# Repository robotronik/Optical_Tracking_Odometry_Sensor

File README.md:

Robotronik Optical Tracking Odometry Sensor
========================================

![Robotronik Optical Tracking Odometry Sensor [SEN-24904]](assets/img/otos_1.png)

[*Robotronik Optical Tracking Odometry Sensor [SEN-24904]*](https://www.sparkfun.com/products/24904)

The Robotronik Optical Tracking Odometry Sensor empowers you to elevate your robot's navigation capabilities with exceptional precision and streamlined integration. This compact, all-in-one sensor leverages the power of the PAA5163E1 chip from PixArt Imaging Inc., delivering accurate dual-axis motion data across various hard floor surfaces. But that's not all! This sensor boasts a powerful built-in 6-axis Inertial Measurement Unit (IMU) and an onboard microcontroller that performs real-time sensor fusion and tracking algorithms.

Repository Contents
-------------------

* **/Hardware** - Kicad 9 Design
* **/Production** - Production panel files

Documentation
--------------
* **[Arduino Library](https://github.com/sparkfun/SparkFun_Qwiic_OTOS_Arduino_Library)** - Arduino library for the SparkFun Optical Tracking Odometry Sensor.
* **[Hookup Guide](https://docs.sparkfun.com/SparkFun_Optical_Tracking_Odometry_Sensor/)** - Hookup guide for the SparkFun Optical Tracking Odometry Sensor.

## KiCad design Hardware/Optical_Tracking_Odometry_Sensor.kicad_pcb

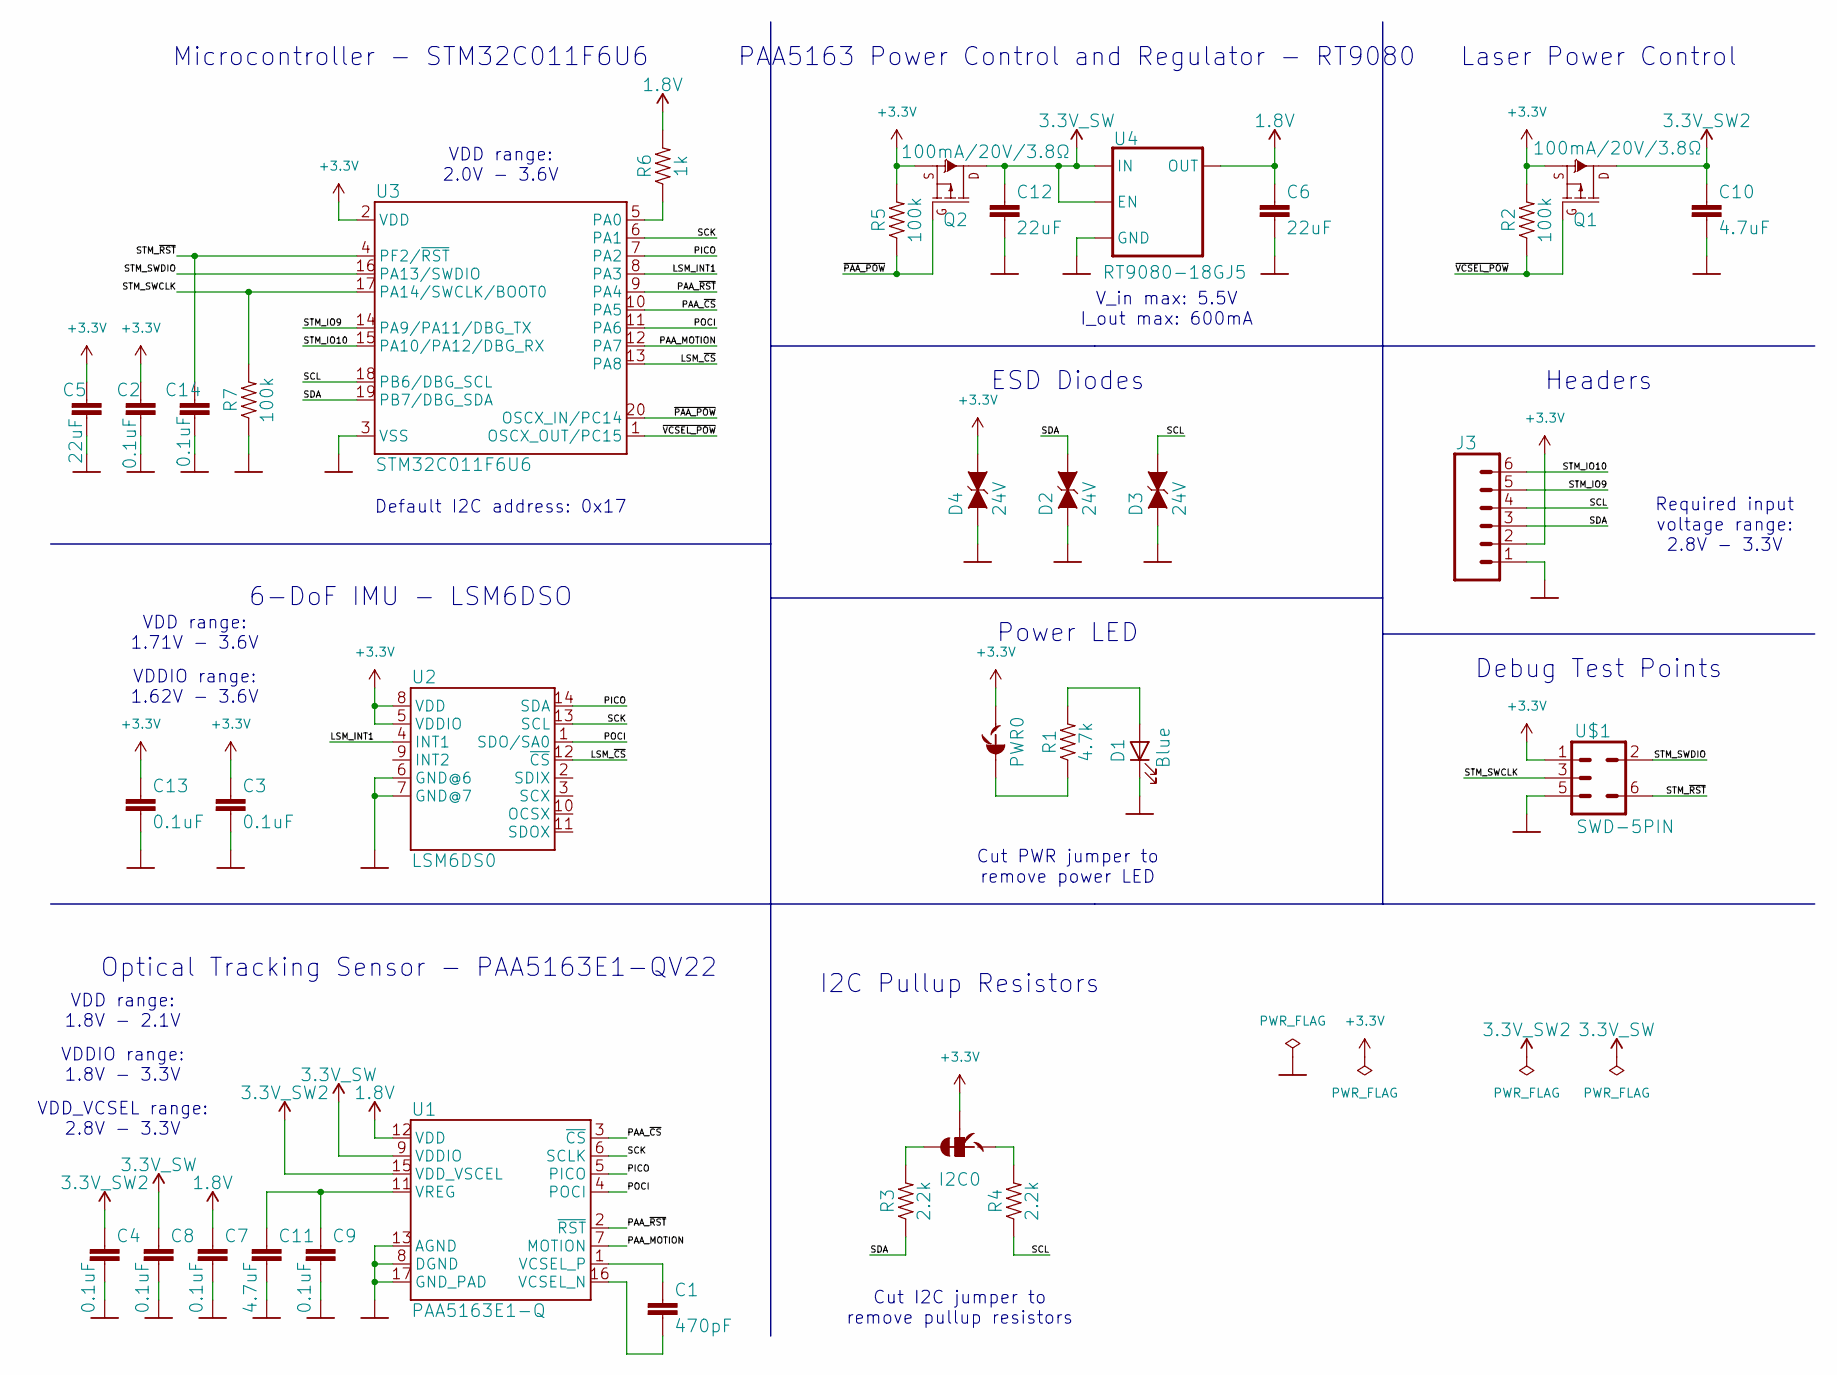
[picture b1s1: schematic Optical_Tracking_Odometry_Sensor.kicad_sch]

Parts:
C1: 470pF; C_0603_1608Metric
C2, C3, C4, C7, C8, C9, C13, C14: 0.1uF; C_0603_1608Metric
C5, C6, C12: 22uF; C_0603_1608Metric
C10, C11: 4.7uF; C_0603_1608Metric
D1: Blue; LED_0603_1608Metric
D2, D3, D4: 24V; D_0603_1608Metric
I2C0: JUMPER-SMT_3_2-NC_TRACE_SILK; SMT-JUMPER_3_2-NC_TRACE_SILK
J3: CONN_06NO_SILK_NO_POP; 1X06_NO_SILK
PWR0: JUMPER-SMT_2_NC_TRACE_SILK; SMT-JUMPER_2_NC_TRACE_SILK
Q1, Q2: 100mA/20V/3.8Ω; SOT-416
R1: 4.7k; R_0603_1608Metric
R2, R5, R7: 100k; R_0603_1608Metric
R3, R4: 2.2k; R_0603_1608Metric
R6: 1k; R_0603_1608Metric
U1: PAA5163E1-Q
U2: LSM6DS0; LGA-14_3x2.5mm_P0.5mm_LayoutBorder3x4y
U3: STM32C011F6U6; ST_UFQFPN-20_3x3mm_P0.5mm
U4: RT9080-18GJ5; SOT-23-5
U$1: SWD-5PIN; PAD_05_03X2_TP_NO4

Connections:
1.8V: C6.1, C7.1, R6.2, U1.12 (VDD), U4.5 (OUT)
3.3V_SW: C8.1, C12.1, Q2.3 (D), U1.9 (VDDIO), U4.1 (IN), U4.3 (EN)
3.3V_SW2: C4.1, C10.1, Q1.3 (D), U1.15 (VDD_VSCEL)
+3.3V: C2.1, C3.1, C5.1, C13.1, D4.2 (C), I2C0.2, J3.2, PWR0.2, Q1.2 (S), Q2.2 (S), R2.2, R5.2, U2.5 (VDDIO), U2.8 (VDD), U3.2 (VDD), U$1.1
/LSM_INT1: U2.4 (INT1), U3.8 (PA3)
/LSM_~CS: U2.12 (~CS), U3.13 (PA8)
/PAA_MOTION: U1.7 (MOTION), U3.12 (PA7)
/PAA_~CS: U1.3 (~CS), U3.10 (PA5)
/PAA_~RST: U1.2 (~RST), U3.9 (PA4)
/PICO: U1.5 (PICO), U2.14 (SDA), U3.7 (PA2)
/POCI: U1.4 (POCI), U2.1 (SDO/SA0), U3.11 (PA6)
/SCK: U1.6 (SCLK), U2.13 (SCL), U3.6 (PA1)
/SCL: D3.2 (C), J3.4, R4.1, U3.18 (PB6/DBG_SCL)
/SDA: D2.2 (C), J3.3, R3.1, U3.19 (PB7/DBG_SDA)
/STM_IO9: J3.5, U3.14 (PA9/PA11/DBG_TX)
/STM_IO10: J3.6, U3.15 (PA10/PA12/DBG_RX)
/STM_SWCLK: R7.2, U3.17 (PA14/SWCLK/BOOT0), U$1.3
/STM_SWDIO: U3.16 (PA13/SWDIO), U$1.2
/STM_~RST: C14.1, U3.4 (PF2/~RST), U$1.6
/~PAA_POW: Q2.1 (G), R5.1, U3.20 (OSCX_IN/PC14)
/~VCSEL_POW: Q1.1 (G), R2.1, U3.1 (OSCX_OUT/PC15)
GND: C2.2, C3.2, C4.2, C5.2, C6.2, C7.2, C8.2, C9.2, C10.2, C11.2, C12.2, C13.2, C14.2, D1.1 (K), D2.1 (A), D3.1 (A), D4.1 (A), J3.1, R7.1, U1.8 (DGND), U1.13 (AGND), U1.17 (GND_PAD), U2.6 (GND@6), U2.7 (GND@7), U3.3 (VSS), U4.2 (GND), U$1.5
unnamed: D1.2 (A), R1.2
unnamed: I2C0.1, R4.2
unnamed: I2C0.3, R3.2
unnamed: PWR0.1, R1.1
unnamed: C1.2, U1.16 (VCSEL_N)
unnamed: C1.1, U1.1 (VCSEL_P)
unnamed: C9.1, C11.1, U1.11 (VREG)
unnamed: R6.1, U3.5 (PA0)

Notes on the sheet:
Power LED
VDD range: 2.0V - 3.6V
I2C Pullup Resistors
6-DoF IMU - LSM6DSO
Microcontroller - STM32C011F6U6
Cut I2C jumper to remove pullup resistors
VDDIO range: 1.62V - 3.6V
VDDIO range: 1.8V - 3.3V
Debug Test Points
Cut PWR jumper to remove power LED
PAA5163 Power Control and Regulator - RT9080
Default I2C address: 0x17
VDD range: 1.8V - 2.1V
Required input voltage range: 2.8V - 3.3V
ESD Diodes
V_in max: 5.5V I_out max: 600mA
Headers
VDD_VCSEL range: 2.8V - 3.3V
Laser Power Control
Optical Tracking Sensor - PAA5163E1-QV22
VDD range: 1.71V - 3.6V

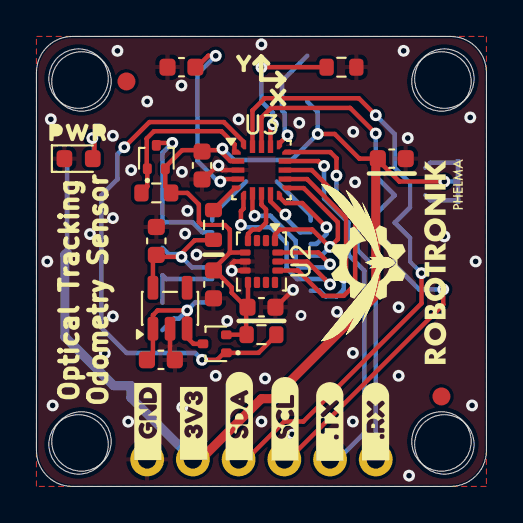
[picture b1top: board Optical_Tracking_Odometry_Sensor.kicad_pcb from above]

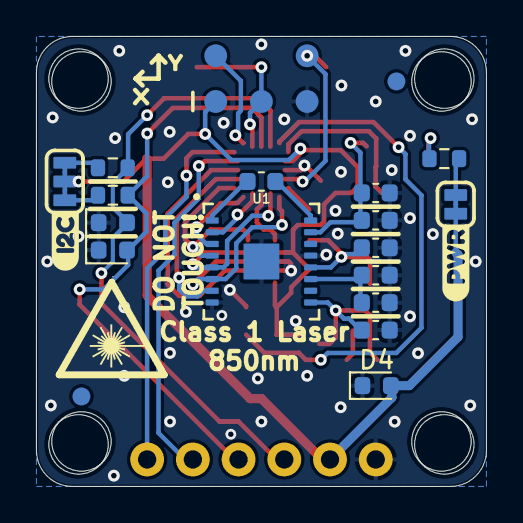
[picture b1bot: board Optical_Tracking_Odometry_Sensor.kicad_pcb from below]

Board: 2 copper layers, 25.0 x 25.0 mm, 58 parts (23 on the bottom side), 30 nets.

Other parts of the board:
FD1, FD2, FD3, FD4: FIDUCIAL1X2; FIDUCIAL-1X2
FRAME1: FRAME-LETTER; CREATIVE_COMMONS
H1, H1#2, H2, H3, H4: STAND-OFF
U$18, U$30: X0
U$25: PWR0
U$29, U$31: Y0
kibuzzard-68FE4A6E: G***; kibuzzard-68FE4A6E
kibuzzard-68FE4A91: G***; kibuzzard-68FE4A91
kibuzzard-68FE4AB9: G***; kibuzzard-68FE4AB9
kibuzzard-68FE4AC0: G***; kibuzzard-68FE4AC0
kibuzzard-68FE4B1F: G***; kibuzzard-68FE4B1F
kibuzzard-68FE4B2A: G***; kibuzzard-68FE4B2A
kibuzzard-68FE49AD: G***; kibuzzard-68FE49AD
kibuzzard-68FE4977: G***; kibuzzard-68FE4977

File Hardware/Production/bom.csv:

Designator,Footprint,Quantity,Value,LCSC Part #
"_34, _33, _32, _31, _30, _29, _28, _27, _26, _25, _24, _23, _22, _21, _20, _19, _18, _17, _16, _15, _14, _13, _12, _11, _10, _9, _8",,27,,
"C1_8, C1_7, C1_6, C1_5, C1_4, C1_3, C1_2, C1",0603,8,470pF,
"C10_8, C10_7, C10_6, C10_5, C10_4, C10_3, C10_2, C10, C11_8, C11_7, C11_6, C11_5, C11_4, C11_3, C11_2, C11",0603,16,4.7uF,
"C12_8, C12_7, C12_6, C12_5, C12_4, C12_3, C12_2, C12, C5_8, C5_7, C5_6, C5_5, C5_4, C5_3, C5_2, C5, C6_8, C6_7, C6_6, C6_5, C6_4, C6_3, C6_2, C6",0603,24,22uF,
"C13_8, C13_7, C13_6, C13_5, C13_4, C13_3, C13_2, C13, C14_8, C14_7, C14_6, C14_5, C14_4, C14_3, C14_2, C14, C2_8, C2_7, C2_6, C2_5, C2_4, C2_3, C2_2, C2, C3_8, C3_7, C3_6, C3_5, C3_4, C3_3, C3_2, C3, C4_8, C4_7, C4_6, C4_5, C4_4, C4_3, C4_2, C4, C7_8, C7_7, C7_6, C7_5, C7_4, C7_3, C7_2, C7, C8_8, C8_7, C8_6, C8_5, C8_4, C8_3, C8_2, C8, C9_8, C9_7, C9_6, C9_5, C9_4, C9_3, C9_2, C9",0603,64,0.1uF,
"D1_8, D1_7, D1_6, D1_5, D1_4, D1_3, D1_2, D1",LED-0603,8,Blue,
"D2_8, D2_7, D2_6, D2_5, D2_4, D2_3, D2_2, D2, D3_8, D3_7, D3_6, D3_5, D3_4, D3_3, D3_2, D3, D4_8, D4_7, D4_6, D4_5, D4_4, D4_3, D4_2, D4",0603,24,24V,
"FD1_9, FD1_8, FD1_7, FD1_6, FD1_5, FD1_4, FD1_3, FD1_2, FD1, FD2_9, FD2_8, FD2_7, FD2_6, FD2_5, FD2_4, FD2_3, FD2_2, FD2, FD3_9, FD3_8, FD3_7, FD3_6, FD3_5, FD3_4, FD3_3, FD3_2, FD3, FD4_9, FD4_8, FD4_7, FD4_6, FD4_5, FD4_4, FD4_3, FD4_2, FD4",FIDUCIAL-1X2,36,FIDUCIAL1X2,
FRAME1,CREATIVE_COMMONS,1,FRAME-LETTER,
"H1_18, H1_17, H1_16, H1_15, H1_14, H1_13, H1_12, H1_11, H1_10, H1_9, H1_8, H1_7, H1_6, H1_5, H1_4, H1_3, H1_2, H1, H2_9, H2_8, H2_7, H2_6, H2_5, H2_4, H2_3, H2_2, H2, H3_9, H3_8, H3_7, H3_6, H3_5, H3_4, H3_3, H3_2, H3, H4_9, H4_8, H4_7, H4_6, H4_5, H4_4, H4_3, H4_2, H4",STAND-OFF,45,STAND-OFF,
"I2C0_8, I2C0_7, I2C0_6, I2C0_5, I2C0_4, I2C0_3, I2C0_2, I2C0",SMT-JUMPER_3_2-NC_TRACE_SILK,8,JUMPER-SMT_3_2-NC_TRACE_SILK,
"J3_11, J3_10, J3_9, J3_8, J3_7, J3_6, J3_5, J3_4, J3_3, J3_2, J3",1X06_NO_SILK,11,CONN_06NO_SILK_NO_POP,
"PWR0_8, PWR0_7, PWR0_6, PWR0_5, PWR0_4, PWR0_3, PWR0_2, PWR0",SMT-JUMPER_2_NC_TRACE_SILK,8,JUMPER-SMT_2_NC_TRACE_SILK,
"Q1_8, Q1_7, Q1_6, Q1_5, Q1_4, Q1_3, Q1_2, Q1, Q2_8, Q2_7, Q2_6, Q2_5, Q2_4, Q2_3, Q2_2, Q2",SOT-416FL,16,100mA/20V/3.8Ω,
"R1_8, R1_7, R1_6, R1_5, R1_4, R1_3, R1_2, R1",0603,8,4.7k,
"R2_8, R2_7, R2_6, R2_5, R2_4, R2_3, R2_2, R2, R5_8, R5_7, R5_6, R5_5, R5_4, R5_3, R5_2, R5, R7_8, R7_7, R7_6, R7_5, R7_4, R7_3, R7_2, R7",0603,24,100k,
"R3_8, R3_7, R3_6, R3_5, R3_4, R3_3, R3_2, R3, R4_8, R4_7, R4_6, R4_5, R4_4, R4_3, R4_2, R4",0603,16,2.2k,
"R6_8, R6_7, R6_6, R6_5, R6_4, R6_3, R6_2, R6",0603,8,1k,
"U$1_9, U$1_8, U$1_7, U$1_6, U$1_5, U$1_4, U$1_3, U$1_2",PAD_05_03X2_TP_NO4,8,SWD-5PIN,
U$1,Pogo_Pins,1,SWD-5PIN,
"U$18_8, U$18_7, U$18_6, U$18_5, U$18_4, U$18_3, U$18_2, U$18, U$30_8, U$30_7, U$30_6, U$30_5, U$30_4, U$30_3, U$30_2, U$30",X0,16,,
"U$25_8, U$25_7, U$25_6, U$25_5, U$25_4, U$25_3, U$25_2, U$25",PWR0,8,,
"U$29_8, U$29_7, U$29_6, U$29_5, U$29_4, U$29_3, U$29_2, U$29, U$31_8, U$31_7, U$31_6, U$31_5, U$31_4, U$31_3, U$31_2, U$31",Y0,16,,
"U1_8, U1_7, U1_6, U1_5, U1_4, U1_3, U1_2, U1",PAA5163E1-Q,8,PAA5163E1-Q,
"U2_8, U2_7, U2_6, U2_5, U2_4, U2_3, U2_2, U2",LGA14L,8,LSM6DS0,
"U3_8, U3_7, U3_6, U3_5, U3_4, U3_3, U3_2, U3",STM32C011F6U6,8,STM32C011F6U6,
"U4_8, U4_7, U4_6, U4_5, U4_4, U4_3, U4_2, U4",SOT23-5,8,RT9080-18GJ5,

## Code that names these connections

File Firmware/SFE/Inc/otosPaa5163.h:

/*
    SPDX-License-Identifier: MIT
    
    Copyright (c) 2024 SparkFun Electronics
*/

#pragma once

#include "main.h"
#include "sfePaa5163.h"
#include "sfeTkStmSPI.h"
#include "adc.h"
#include "time.h"

class PAA5163 : public sfePaa5163
{
  public:
    sfeTkError_t begin()
    {
        // First we need to power up the PAA5163
        sfeTkError_t err = powerUpSequence();
        if(err != kSTkErrOk)
            return err;

        // Now we need SPI, so initialize the SPI bus
        err = _spiBus.init(PAA_CS_GPIO_Port, PAA_CS_Pin, false);
        if(err != kSTkErrOk)
            return err;

        return sfePaa5163::begin(&_spiBus);
    }
    sfeTkError_t powerUpSequence()
    {
        // 1. Apply power to VDD and VDDIO (any order, max 100ms apart)
        // Note: VDD_VCSEL should be powered on together with the second supply
        LL_GPIO_ResetOutputPin(PAA_POW_GPIO_Port, PAA_POW_Pin);
        LL_GPIO_ResetOutputPin(VCSEL_POW_GPIO_Port, VCSEL_POW_Pin); // Updated: PAA5163 sequence [cite: 138]

        // Wait for voltage stabilization (Datasheet step 2: Wait at least 50ms) 
        delayMillis(50);

        // 2. Measure the 1.8V net (PAA5163 VDD range is 1.8V to 2.1V) [cite: 135]
        uint16_t adcMillivolts;
        if(readADCMillivolts(adcMillivolts) == false)
            return kSTkErrFail;
        if (adcMillivolts < 1700 || adcMillivolts > 2150) // Range adjusted for 5163 specs [cite: 135]
        {
            return kSTkErrFail;
        }

        // 3. Reset SPI Port: Drive NCS high for at least 0.1ms 
        LL_GPIO_SetOutputPin(GPIOA, LL_GPIO_PIN_5); // Assuming Pin 5 is NCS
        delayMicroseconds(100); 

        // 4. Hardware Reset: Assert NRST for >20 microseconds [cite: 142, 173]
        LL_GPIO_ResetOutputPin(PAA_RST_GPIO_Port, PAA_RST_Pin);
        delayMicroseconds(20);
        LL_GPIO_SetOutputPin(PAA_RST_GPIO_Port, PAA_RST_Pin);

        // 5. Post-Reset Delay: Datasheet requires 120ms for valid motion after reset 
        // (If you use software reset 0x3A later, this delay is mandatory)
        delayMillis(120);

        return kSTkErrOk;
    }

  protected:
    void delayMillis(uint32_t milliseconds)
    {
        delay(milliseconds);
    }

  private:
    // SPI interface
    sfeTkStmSPI _spiBus;
};

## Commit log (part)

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2025-06-21 Readme
2025-06-21 Improvements
2025-06-22 Good
2025-10-30 yepyep
2025-11-20 tinty tiny
2026-04-13 added registers
2026-04-13 Added more debug signals
2026-05-16 Volatile bugfix
